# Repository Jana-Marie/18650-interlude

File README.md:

# 18650-interlude

A very simple board to measure the current from a 18650 battery cell for power profiling.

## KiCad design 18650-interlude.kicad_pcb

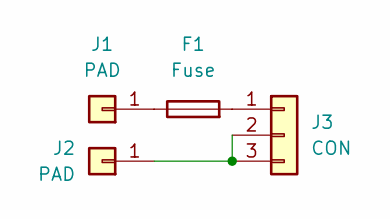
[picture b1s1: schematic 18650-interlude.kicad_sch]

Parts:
F1: Fuse; R_0805
J1, J2: PAD; 18650-pad
J3: CON; PinHeader_1x03_P2.54mm_Vertical

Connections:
unnamed: F1.1, J1.1
unnamed: F1.2, J3.1
unnamed: J2.1, J3.2, J3.3

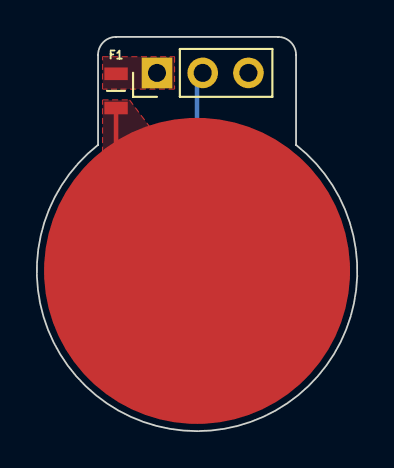
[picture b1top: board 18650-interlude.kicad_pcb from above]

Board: 2 copper layers, 17.8 x 21.9 mm, 4 parts (1 on the bottom side), 3 nets.

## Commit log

2022-11-27 added image
2022-11-27 added gitignore
2022-11-27 added kicad files
2022-11-27 added schematic
2022-11-27 added schematic to readme
2022-11-27 added license
